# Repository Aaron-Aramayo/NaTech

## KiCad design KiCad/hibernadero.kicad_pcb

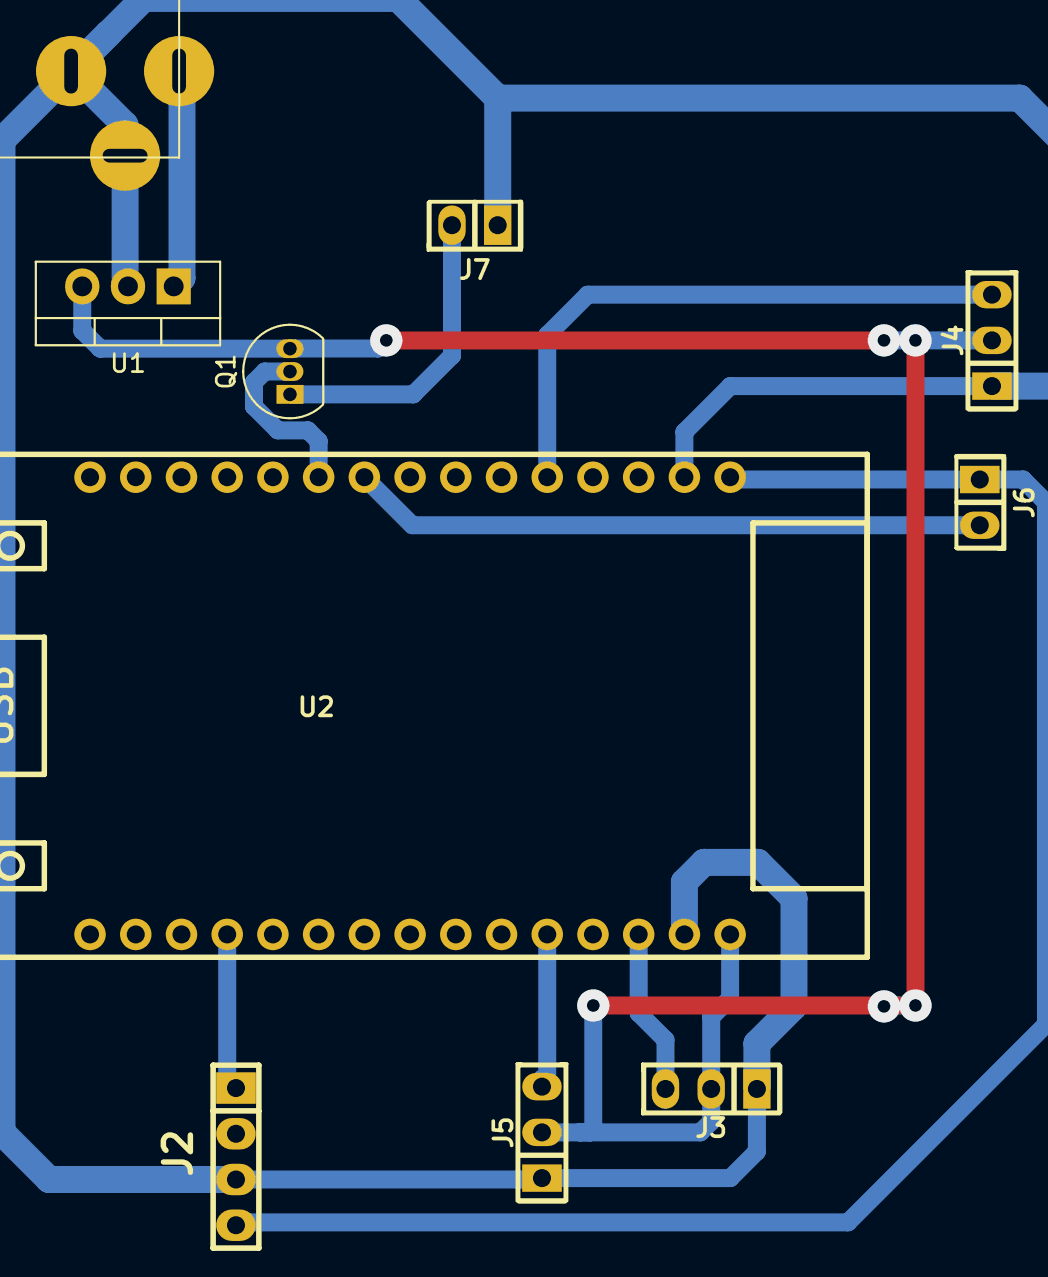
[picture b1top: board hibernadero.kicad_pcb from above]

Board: 2 copper layers, 10 parts (0 on the bottom side), 11 nets.

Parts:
J1: jack; Jack_hembra_DC_barrel
J2: Sensor de humedad de tierra; pin_strip_4
J3: Bomba de aire; Pin_Strip_3_90
J4: Sensor Temperatura+Humedad Amb; Pin_Strip_3_90
J5: Dimmer Led; Pin_Strip_3_90
J6: Boya de agua; Pin_Strip_2_90
J7: Bomba de agua; Pin_Strip_2_90
Q1: PN2222A; TO-92_Inline
U1: LM7805_TO220; TO-220-3_Vertical
U2: ESP32-DEVKIT-V1; ESP32_DevKit_V1_CH9102X

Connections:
/3V3: J2.4, J6.1, U2.1 (3V3)
/5V: J3.2, J4.2, J5.2, Q1.3 (C), U1.3 (VO), U2.30 (VIN)
/AIRPUMP: J3.3, U2.28 (D13)
/DHT11: J4.3, U2.5 (D4)
/DIMLED: J5.3, U2.26 (D14)
/GND: J1.2, J1.3, J2.3, J3.1, J4.1, J5.1, J7.1, U1.2 (GND), U2.2 (GND), U2.29 (GND)
/WATERINDICATOR: J6.2, U2.9 (D18)
/WATERPUMP: Q1.2 (B), U2.10 (D19)
/YL69: J2.1, U2.19 (D34)
unnamed: J7.2, Q1.1 (E)
unnamed: J1.1, U1.1 (VI)

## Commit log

2022-09-16 Create i
